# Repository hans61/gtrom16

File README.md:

"# gtrom16" 

Switcher for 16 Gigatron ROM versions

The switch stores the last selected ROM in the EEPROM of the ATtiny24. This allows a reset by switching the Gigatron off/on. I have found only 10 different ROMs so far (v1, v2, v3, v4, v5a, v6, vX0, v7, 128k7, (512k7)).
When storing in EEPROM, I rotate the cells so that 6,300,000 ROM changes should be possible.

schematic

PCB

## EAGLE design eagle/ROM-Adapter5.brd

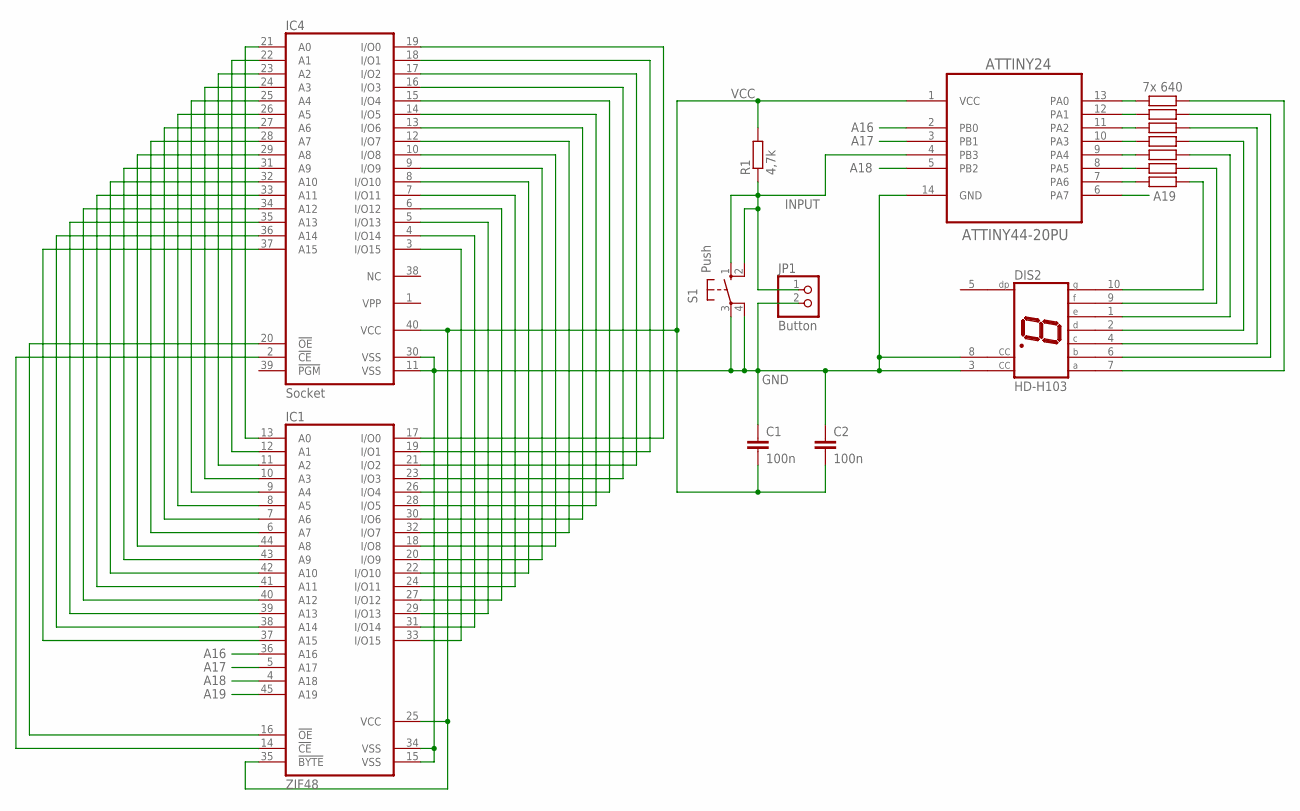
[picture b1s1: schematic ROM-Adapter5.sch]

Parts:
ATTINY24: ATTINY44-20PU; DIP254P762X533-14
C1, C2: 100n; C025-030X050
DIS2: HD-H103; HDSP-M
IC1: ZIF48; MEMORY-HITACHI_ZIF48
IC4: Socket; DIL40
JP1: Button; 1X02
R1: 4,7k; 0207/10
R2: 7x 640; 0207/10
R3, R4, R5, R6, R7, R8: 640; 0207/10
S1: Push; B3F-10XX

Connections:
A16: ATTINY24.2 (PB0), IC1.36 (A16)
A17: ATTINY24.3 (PB1), IC1.5 (A17)
A18: ATTINY24.5 (PB2), IC1.4 (A18)
A19: ATTINY24.6 (PA7), IC1.45 (A19)
GND: ATTINY24.14 (GND), C1.1, C2.1, DIS2.3 (CC), DIS2.8 (CC), IC1.15 (VSS), IC1.34 (VSS), IC4.11 (VSS), IC4.30 (VSS), JP1.2, S1.3, S1.4 (P1)
INPUT: ATTINY24.4 (PB3), JP1.1, R1.1, S1.1 (S), S1.2 (S1)
unnamed: IC1.13 (A0), IC4.21 (A0)
unnamed: IC1.12 (A1), IC4.22 (A1)
unnamed: ATTINY24.13 (PA0), R2.1
unnamed: IC1.11 (A2), IC4.23 (A2)
unnamed: IC1.10 (A3), IC4.24 (A3)
unnamed: IC1.9 (A4), IC4.25 (A4)
unnamed: IC1.8 (A5), IC4.26 (A5)
unnamed: IC1.7 (A6), IC4.27 (A6)
unnamed: IC1.6 (A7), IC4.28 (A7)
unnamed: IC1.44 (A8), IC4.29 (A8)
unnamed: IC1.43 (A9), IC4.31 (A9)
unnamed: IC1.42 (A10), IC4.32 (A10)
unnamed: IC1.41 (A11), IC4.33 (A11)
unnamed: IC1.40 (A12), IC4.34 (A12)
unnamed: IC1.39 (A13), IC4.35 (A13)
unnamed: IC1.38 (A14), IC4.36 (A14)
unnamed: IC1.37 (A15), IC4.37 (A15)
unnamed: IC1.16 (!OE), IC4.20 (!OE)
unnamed: IC1.14 (!CE), IC4.2 (!CE)
unnamed: DIS2.10 (G), R8.2
unnamed: IC1.33 (I/O15), IC4.3 (I/O15)
unnamed: DIS2.9 (F), R7.2
unnamed: IC1.31 (I/O14), IC4.4 (I/O14)
unnamed: IC1.29 (I/O13), IC4.5 (I/O13)
unnamed: IC1.27 (I/O12), IC4.6 (I/O12)
unnamed: IC1.24 (I/O11), IC4.7 (I/O11)
unnamed: IC1.22 (I/O10), IC4.8 (I/O10)
unnamed: IC1.20 (I/O9), IC4.9 (I/O9)
unnamed: IC1.18 (I/O8), IC4.10 (I/O8)
unnamed: IC1.32 (I/O7), IC4.12 (I/O7)
unnamed: IC1.30 (I/O6), IC4.13 (I/O6)
unnamed: IC1.28 (I/O5), IC4.14 (I/O5)
unnamed: IC1.26 (I/O4), IC4.15 (I/O4)
unnamed: IC1.23 (I/O3), IC4.16 (I/O3)
unnamed: IC1.21 (I/O2), IC4.17 (I/O2)
unnamed: IC1.19 (I/O1), IC4.18 (I/O1)
unnamed: IC1.17 (I/O0), IC4.19 (I/O0)
unnamed: ATTINY24.12 (PA1), R3.1
unnamed: ATTINY24.11 (PA2), R4.1
unnamed: ATTINY24.10 (PA3), R5.1
unnamed: ATTINY24.9 (PA4), R6.1
unnamed: ATTINY24.8 (PA5), R7.1
unnamed: ATTINY24.7 (PA6), R8.1
unnamed: DIS2.1 (E), R6.2
unnamed: DIS2.2 (D), R5.2
unnamed: DIS2.4 (C), R4.2
unnamed: DIS2.6 (B), R3.2
unnamed: DIS2.7 (A), R2.2
VCC: ATTINY24.1 (VCC), C1.2, C2.2, IC1.25 (VCC), IC1.35 (!BYTE), IC4.40 (VCC), R1.2

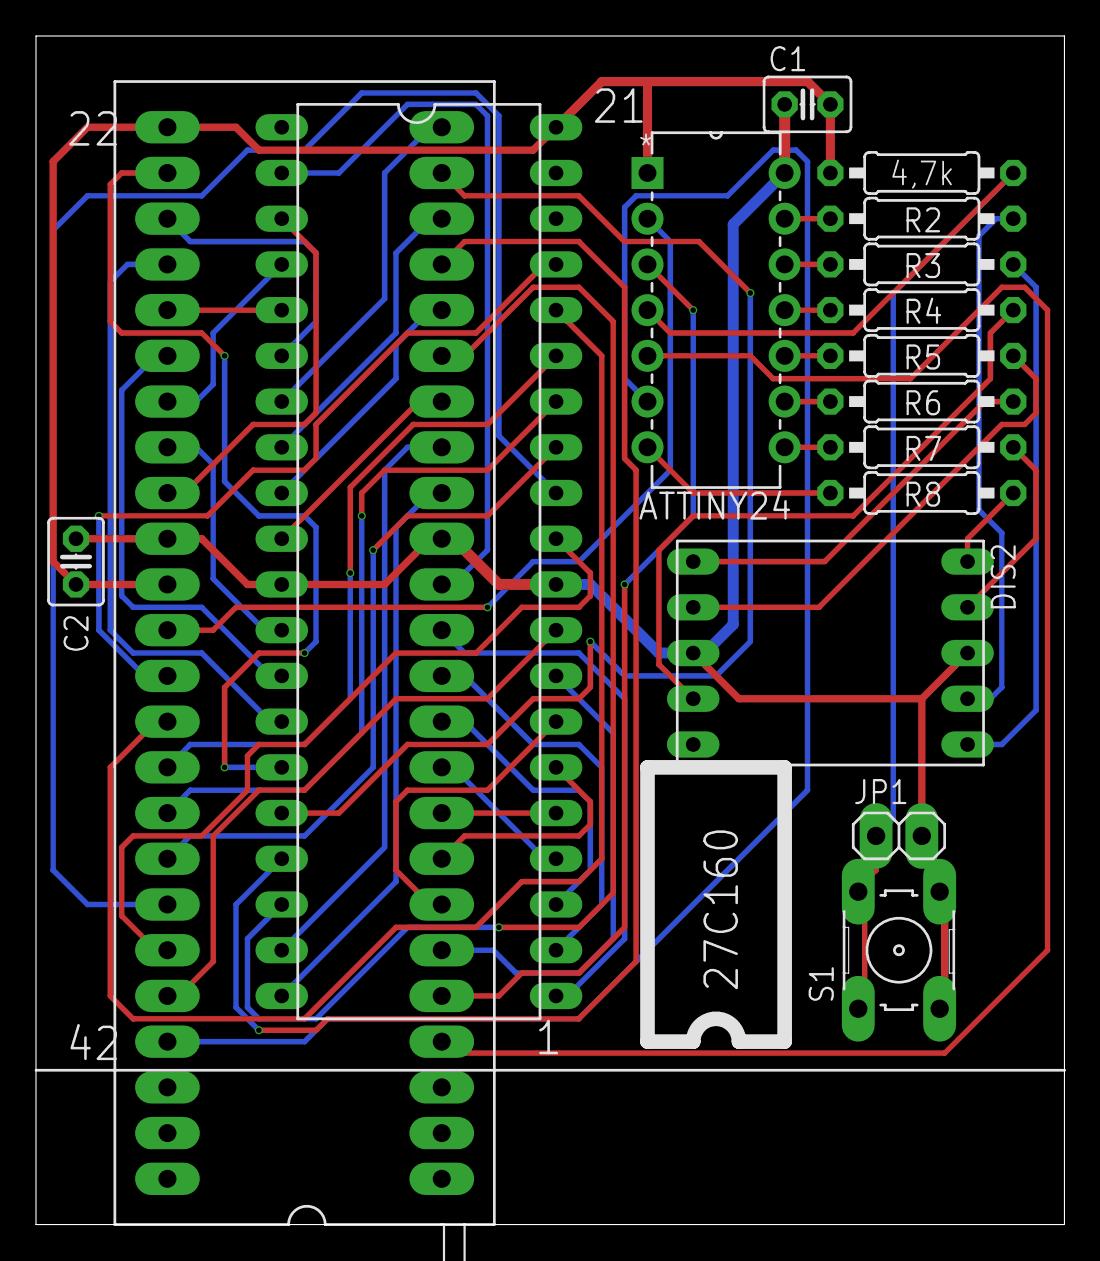
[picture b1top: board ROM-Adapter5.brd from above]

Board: 2 copper layers, 57.1 x 66.0 mm, 16 parts (0 on the bottom side), 55 nets.

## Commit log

2023-05-01 first version, tested, needs improvement
2023-05-04 new version, tested
2023-05-23 ROM Files added for burning
